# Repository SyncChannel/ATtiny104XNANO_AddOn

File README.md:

# ATtiny104XNANO_AddOn

Learning Embedded Electronics with the Atmel ATtiny104 Xplained NANO

See my blog post for more information:

http://syncchannel.blogspot.com/2016/05/learning-embedded-electronics-with.html

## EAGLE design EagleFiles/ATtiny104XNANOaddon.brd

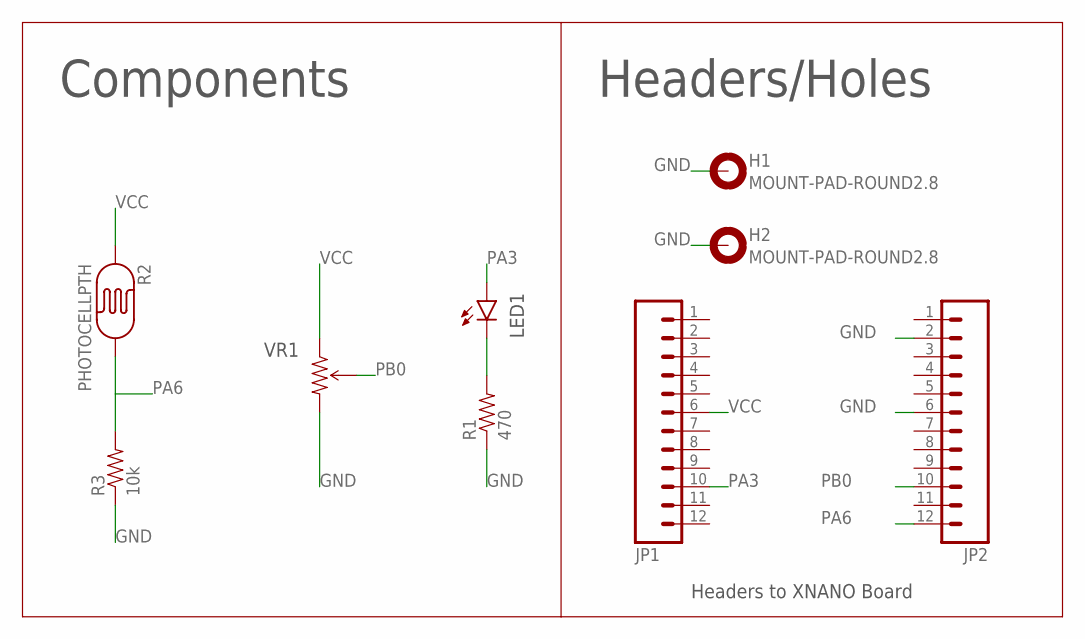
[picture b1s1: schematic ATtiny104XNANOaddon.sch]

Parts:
D1: LED5MM
H1, H2: MOUNT-PAD-ROUND2.8; 2,8-PAD
JP1, JP2: M12NO_SILK; 1X12_NO_SILK
R1: 470; AXIAL-0.4
R2: PHOTOCELLPTH; PHOTOCELL
R3: 10k; AXIAL-0.4
R4: TRIMPOT-PTH-KNOB; 3386U

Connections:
GND: H1.B2,8, H2.B2,8, JP2.2, JP2.6, R1.P$1 (1), R3.P$1 (1), R4.3 (CW)
LED1: D1.K (C), R1.P$2 (2)
PA3: D1.A, JP1.10
PA6: JP2.12, R2.2, R3.P$2 (2)
PB0: JP2.10, R4.2 (WIPER)
VCC: JP1.6, R2.1, R4.1 (CCW)

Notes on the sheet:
Headers to XNANO Board
VR1
Components
Headers/Holes
LED1

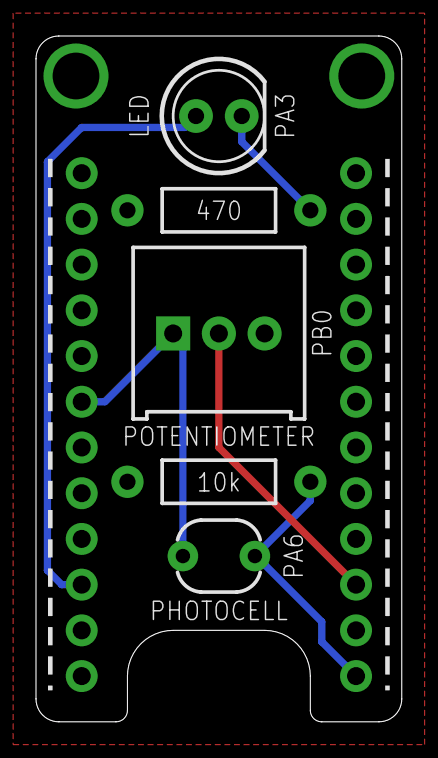
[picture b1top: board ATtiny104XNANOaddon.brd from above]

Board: 2 copper layers, 20.3 x 38.1 mm, 10 parts (1 on the bottom side), 6 nets.

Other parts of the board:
U$1: OSHW-LOGO-S

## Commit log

2016-05-02 :confetti_ball: Added .gitattributes & .gitignore files
2016-05-02 Added Eagle files and documentation
2016-05-02 Update documentation
2016-05-11 Updated Readme with blog post URL

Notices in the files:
parts and their libraries:
SparkFun-Resistors: Licensing: Creative Commons ShareAlike 4.0 International - https://creativecommons.org/licenses/by-sa/4.0
